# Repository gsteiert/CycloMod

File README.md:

# CycloMod
Cyclone 10LP plus RP2350 in SparkFun MicroMod form-factor

Be sure to subscribe to the [Cyclomod Crowd Supply Campaign](https://www.crowdsupply.com/steiert-solutions/cyclomod) for updates on when and how to get CycloMod.

CycloMod brings the flexibility of an FPGA to the SparkFun MicroMod ecosystem.  It combines the Raspberry Pi RP2350 with the Altera Cyclone 10LP, in a compact, adaptable module.  

The FPGA and MCU are designed to be used together.  Most of the MicroMod I/O are connected to the FPGA for highest flexibility, while some functions like USB, ADC and SWD take advantage of the dedicated peripherals in the RP2350.  A few signals, like reset and the primary I2C bus, are connected to both devices.

Most of the RP2350 I/O are connected to Cyclone 10LP.  The MCU is connected to the JTAG pins of the FPGA so that the same flash can store the MCU firmware and FPGA images to be loaded with the Altera JBC player.  GPIO on the FPGA are connected to the MCU QSPI interface to provide a reasonable speed data path between the two devices.  The HSTX port is also connected for higher speed streaming from the MCU to the FPGA.  Input and Output clocks are also connected between the two devices to allow for sharing the 12MHz refernce crystal from the MCU and PLLs in the FPGA.  

The primary intended use case is for the RP2350 to manage the loading of the FPGA to eliminate the need for an additional storage device.  The active serial configuration pins are connected to the SPI port pins on the MicroMod card edge and there is a solder bridge selector that can be cut and shorted to enable laoding the FPGA from external SPI flash.

FPGA images can be transfered to flash over USB using the UF2 flash loader built into the RP2350 ROM.  Altera provides a [JAM Byte Code player](https://github.com/steieio/altera-jbc-player) that can be used to load the FPGA over JTAG.  A [script is available to combine the JBC file with the RP2350 firmware in a single UF2 file](https://github.com/steieio/jbcuf2).  This methodology was demonstrated in the ["Build a $5 FPGA loader" workshop at Crowd Supply Teardown 2024](https://www.crowdsupply.com/teardown/portland-2024/workshop/build-a-5-fpga-loader).

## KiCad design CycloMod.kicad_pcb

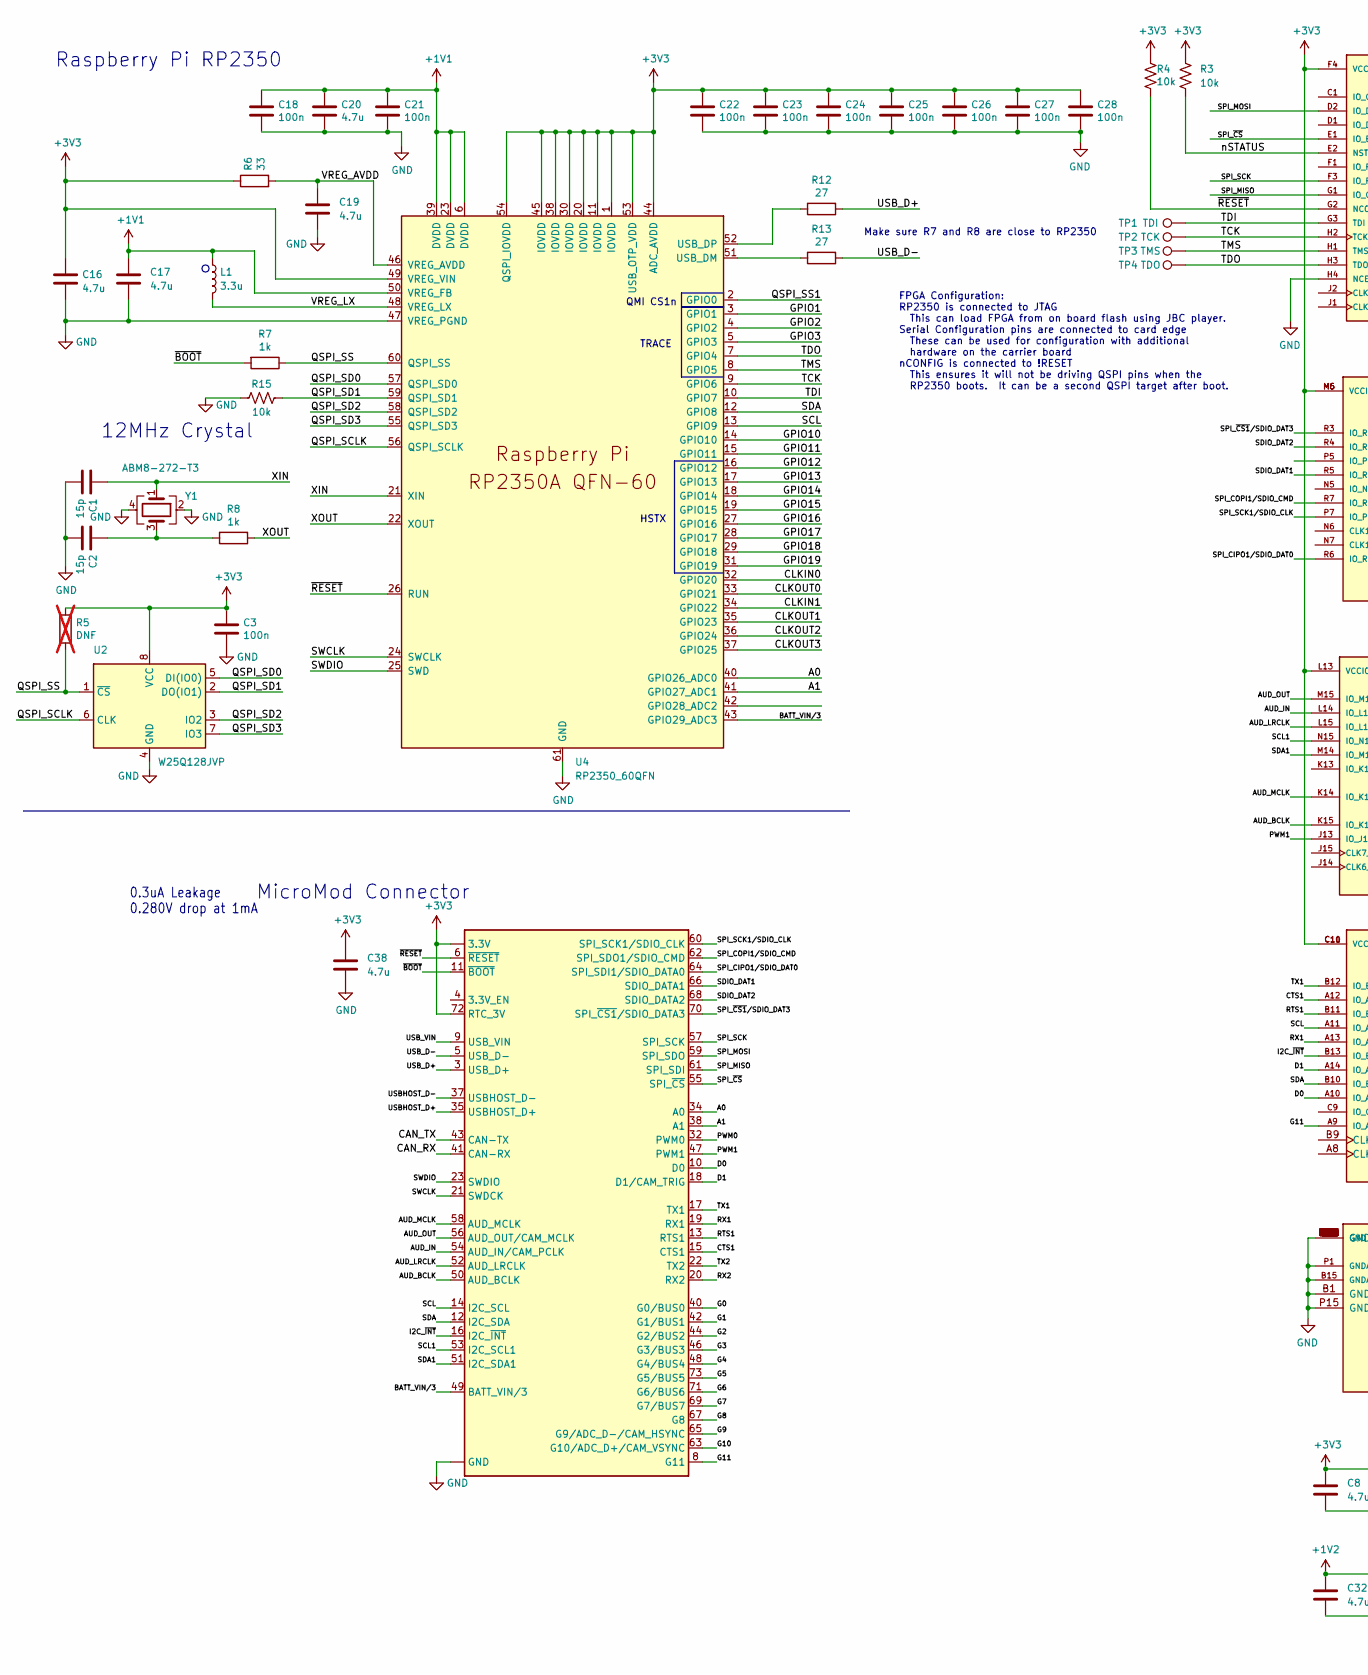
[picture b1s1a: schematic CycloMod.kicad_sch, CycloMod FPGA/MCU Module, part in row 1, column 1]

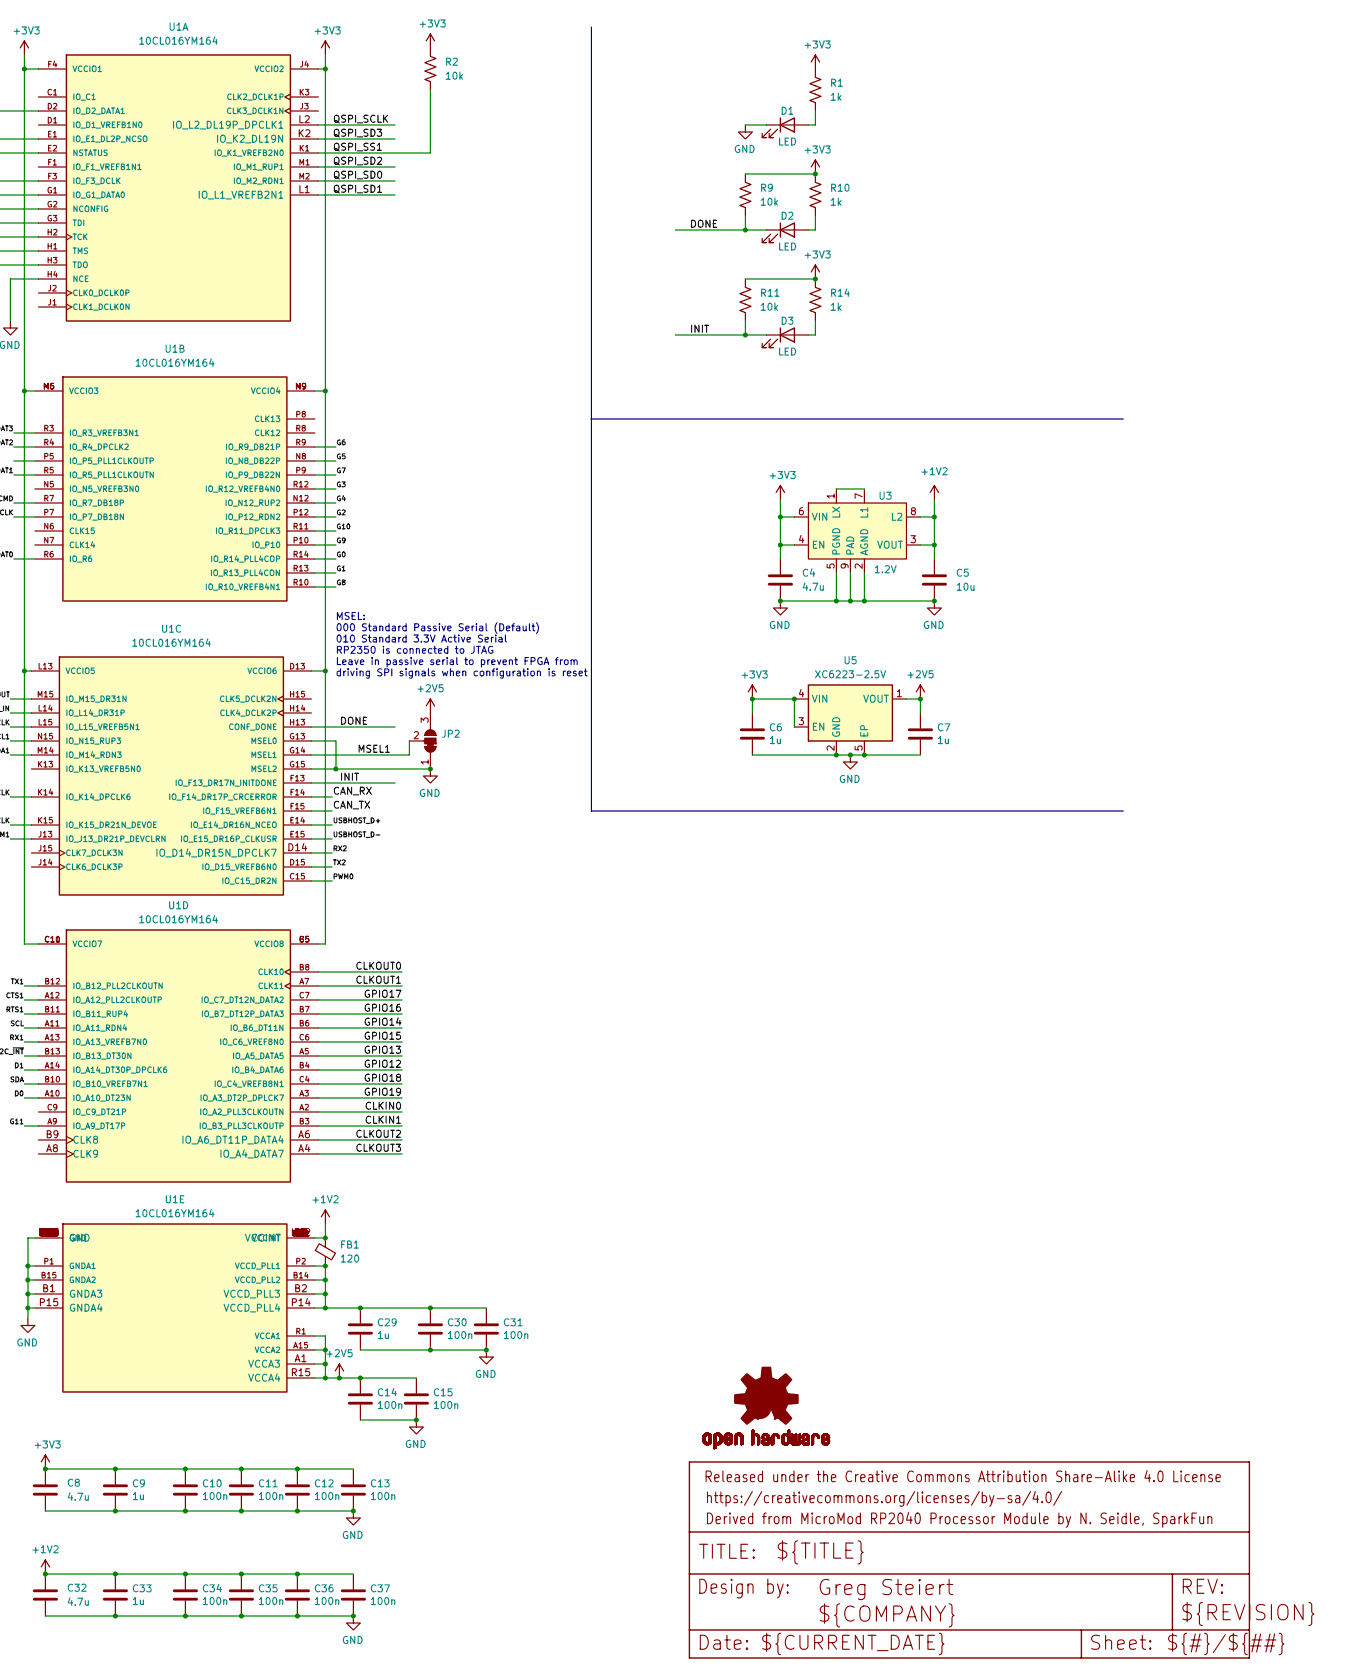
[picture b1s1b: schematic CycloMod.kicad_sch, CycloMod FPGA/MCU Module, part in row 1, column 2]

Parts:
C1, C2: 15p; C_0201_0603Metric; MPN CC0201JRNPO9BN150; LCSC C277480
C3, C10, C11, C12, C13, C14, C15, C18, C21, C22, C23, C24, C25, C26, C27, C28, C30, C31, C34, C35, C36, C37: 100n; C_0201_0603Metric; MPN GRM033R61A104KE15D; LCSC C76934
C4, C8, C19, C20, C32, C38: 4.7u; C_0402_1005Metric; MPN CL05A475MQ5NRNC; LCSC C307423
C5: 10u; C_0402_1005Metric; MPN CL05A106MQ5NUNC; LCSC C15525
C6, C7, C9, C29, C33: 1u; C_0402_1005Metric; MPN CL05A105KP5NNNC; LCSC C14445
C16, C17: 4.7u; C_0402_1005Metric_small_pads; MPN CL05A475MQ5NRNC; LCSC C307423
D1, D2, D3: LED; LED_0402_1005Metric; MPN IN-S42BT5B; LCSC C6968967
FB1: 120; R_0402_1005Metric; MPN BLM15AG121SN1D; LCSC C85812
FRAME1: FRAME-LEDGER; CREATIVE_COMMONS
J1: MICROMOD-2222; MicroMod_Processor
JP2: SolderJumper_3_Bridged12; SolderJumper-3pin_Bridged_RoundedPad_0402
L1: 3.3u; L_pol_2016; MPN AOTA-B201610S3R3-101-T; LCSC C42411119
LOGO3: OSHW-LOGOMINI; OSHW-LOGO-MINI
R1, R7, R8, R10, R14: 1k; R_0201_0603Metric; MPN RC0201FR-071KL; LCSC C138165
R2, R3, R4, R9, R11, R15: 10k; R_0201_0603Metric; MPN RC0201FR-0710KL; LCSC C106225
R5: DNF; R_0201_0603Metric; not fitted
R6: 33; R_0201_0603Metric; MPN RC0201FR-0733RL; LCSC C295794
R12, R13: 27; R_0201_0603Metric; MPN RC0201FR-0727RL; LCSC C273268
TP1: TDI; TestPoint_Pad_D0.5mm
TP2: TCK; TestPoint_Pad_D0.5mm
TP3: TMS; TestPoint_Pad_D0.5mm
TP4: TDO; TestPoint_Pad_D0.5mm
U1: 10CL016YM164; M164_8.0x8.0mm_0.5mm; PARTREV 2019.03.29; LCSC C6063581
U2: W25Q128JVP; WSON-8-1EP_6x5mm_P1.27mm_EP3.4x4.3mm; MPN W25Q128JVPIQ; LCSC C190862
U3: 1.2V; CL-2025-02; MPN XCL239B123FR-G; LCSC C6036085
U4: RP2350_60QFN; RP2350-QFN-60-1EP_7x7_P0.4mm_EP3.4x3.4mm_ThermalVias; MPN RP2350A; LCSC C42411118
U5: XC6223-2.5V; UDFN-4-1EP_1x1mm_P0.65mm_EP0.48x0.48mm; MPN XC6233H2519R-G; LCSC C6934286
Y1: ABM8-272-T3; Crystal_SMD_3225-4Pin_3.2x2.5mm; MPN ABM8-272-T3; LCSC C20625731

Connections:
+1V1: C17.1, C18.1, C20.1, C21.1, L1.1, U4.6 (DVDD), U4.23 (DVDD), U4.39 (DVDD), U4.50 (VREG_FB)
+1V2: C5.1, C32.1, C33.1, C34.1, C35.1, C36.1, C37.1, FB1.1, U1.D3 (VCCINT), U1.D6 (VCCINT), U1.D8 (VCCINT), U1.D10 (VCCINT), U1.F12 (VCCINT), U1.H12 (VCCINT), U1.K12 (VCCINT), U1.L3 (VCCINT), U1.M8 (VCCINT), U1.M11 (VCCINT), U1.N2 (VCCINT), U1.P3 (VCCINT), U3.3 (VOUT), U3.8 (L2)
+2V5: C7.1, C14.1, C15.1, JP2.3 (B), U1.A1 (VCCA3), U1.A15 (VCCA2), U1.R1 (VCCA1), U1.R15 (VCCA4), U5.1 (VOUT)
+3V3: C3.1, C4.1, C6.1, C8.1, C9.1, C10.1, C11.1, C12.1, C13.1, C16.1, C22.1, C23.1, C24.1, C25.1, C26.1, C27.1, C28.1, C38.1, J1.2 (3.3V), J1.72 (RTC_3V), J1.74 (3.3V), R1.1, R2.1, R3.1, R4.1, R5.1, R6.1, R9.1, R10.1, R11.1, R14.1, U1.B5 (VCCIO8), U1.C5 (VCCIO8), U1.C10 (VCCIO7), U1.C11 (VCCIO7), U1.D13 (VCCIO6), U1.F4 (VCCIO1), U1.J4 (VCCIO2), U1.L13 (VCCIO5), U1.M5 (VCCIO3), U1.M6 (VCCIO3), U1.M9 (VCCIO4), U1.N9 (VCCIO4), U2.8 (VCC), U3.4 (EN), U3.6 (VIN), U4.1 (IOVDD), U4.11 (IOVDD), U4.20 (IOVDD), U4.30 (IOVDD), U4.38 (IOVDD), U4.44 (ADC_AVDD), U4.45 (IOVDD), U4.49 (VREG_VIN), U4.53 (USB_OTP_VDD), U4.54 (QSPI_IOVDD), U5.3 (EN), U5.4 (VIN)
/A0: J1.34 (A0), U4.40 (GPIO26_ADC0)
/A1: J1.38 (A1), U4.41 (GPIO27_ADC1)
/AUD_BCLK: J1.50 (AUD_BCLK), U1.K15 (IO_K15_DR21N_DEVOE)
/AUD_IN: J1.54 (AUD_IN/CAM_PCLK), U1.L14 (IO_L14_DR31P)
/AUD_LRCLK: J1.52 (AUD_LRCLK), U1.L15 (IO_L15_VREFB5N1)
/AUD_MCLK: J1.58 (AUD_MCLK), U1.K14 (IO_K14_DPCLK6)
/AUD_OUT: J1.56 (AUD_OUT/CAM_MCLK), U1.M15 (IO_M15_DR31N)
/BATT_VIN/3: J1.49 (BATT_VIN/3), U4.43 (GPIO29_ADC3)
/CAN_RX: J1.41 (CAN-RX), U1.F14 (IO_F14_DR17P_CRCERROR)
/CAN_TX: J1.43 (CAN-TX), U1.F15 (IO_F15_VREFB6N1)
/CLKIN0: U1.A2 (IO_A2_PLL3CLKOUTN), U4.32 (GPIO20)
/CLKIN1: U1.B3 (IO_B3_PLL3CLKOUTP), U4.34 (GPIO22)
/CLKOUT0: U1.B8 (CLK10), U4.33 (GPIO21)
/CLKOUT1: U1.A7 (CLK11), U4.35 (GPIO23)
/CLKOUT2: U1.A6 (IO_A6_DT11P_DATA4), U4.36 (GPIO24)
/CLKOUT3: U1.A4 (IO_A4_DATA7), U4.37 (GPIO25)
/CTS1: J1.15 (CTS1), U1.A12 (IO_A12_PLL2CLKOUTP)
/D0: J1.10 (D0), U1.A10 (IO_A10_DT23N)
/D1: J1.18 (D1/CAM_TRIG), U1.A14 (IO_A14_DT30P_DPCLK6)
/DONE: D2.1 (K), R9.2, U1.H13 (CONF_DONE)
/G0: J1.40 (G0/BUS0), U1.R14 (IO_R14_PLL4COP)
/G1: J1.42 (G1/BUS1), U1.R13 (IO_R13_PLL4CON)
/G2: J1.44 (G2/BUS2), U1.P12 (IO_P12_RDN2)
/G3: J1.46 (G3/BUS3), U1.R12 (IO_R12_VREFB4N0)
/G4: J1.48 (G4/BUS4), U1.N12 (IO_N12_RUP2)
/G5: J1.73 (G5/BUS5), U1.N8 (IO_N8_DB22P)
/G6: J1.71 (G6/BUS6), U1.R9 (IO_R9_DB21P)
/G7: J1.69 (G7/BUS7), U1.P9 (IO_P9_DB22N)
/G8: J1.67 (G8), U1.R10 (IO_R10_VREFB4N1)
/G9: J1.65 (G9/ADC_D-/CAM_HSYNC), U1.P10 (IO_P10)
/G10: J1.63 (G10/ADC_D+/CAM_VSYNC), U1.R11 (IO_R11_DPCLK3)
/G11: J1.8 (G11), U1.A9 (IO_A9_DT17P)
/GPIO1: U4.3 (GPIO1)
/GPIO2: U4.4 (GPIO2)
/GPIO3: U4.5 (GPIO3)
/GPIO10: U4.14 (GPIO10)
/GPIO11: U4.15 (GPIO11)
/GPIO12: U1.B4 (IO_B4_DATA6), U4.16 (GPIO12)
/GPIO13: U1.A5 (IO_A5_DATA5), U4.17 (GPIO13)
/GPIO14: U1.B6 (IO_B6_DT11N), U4.18 (GPIO14)
/GPIO15: U1.C6 (IO_C6_VREF8N0), U4.19 (GPIO15)
/GPIO16: U1.B7 (IO_B7_DT12P_DATA3), U4.27 (GPIO16)
/GPIO17: U1.C7 (IO_C7_DT12N_DATA2), U4.28 (GPIO17)
/GPIO18: U1.C4 (IO_C4_VREFB8N1), U4.29 (GPIO18)
/GPIO19: U1.A3 (IO_A3_DT2P_DPLCK7), U4.31 (GPIO19)
/I2C_~INT: J1.16 (I2C_~INT), U1.B13 (IO_B13_DT30N)
/INIT: D3.1 (K), R11.2, U1.F13 (IO_F13_DR17N_INITDONE)
/MSEL1: JP2.2 (C), U1.G14 (MSEL1)
/PWM0: J1.32 (PWM0), U1.C15 (IO_C15_DR2N)
/PWM1: J1.47 (PWM1), U1.J13 (IO_J13_DR21P_DEVCLRN)
/QSPI_SCLK: U1.L2 (IO_L2_DL19P_DPCLK1), U2.6 (CLK), U4.56 (QSPI_SCLK)
/QSPI_SD0: U1.M2 (IO_M2_RDN1), U2.5 (DI(IO0)), U4.57 (QSPI_SD0)
/QSPI_SD1: R15.2, U1.L1 (IO_L1_VREFB2N1), U2.2 (DO(IO1)), U4.59 (QSPI_SD1)
/QSPI_SD2: U1.M1 (IO_M1_RUP1), U2.3 (IO2), U4.58 (QSPI_SD2)
/QSPI_SD3: U1.K2 (IO_K2_DL19N), U2.7 (IO3), U4.55 (QSPI_SD3)
/QSPI_SS: R5.2, R7.1, U2.1 (~CS), U4.60 (QSPI_SS)
/QSPI_SS1: R2.2, U1.K1 (IO_K1_VREFB2N0), U4.2 (GPIO0)
/RTS1: J1.13 (RTS1), U1.B11 (IO_B11_RUP4)
/RX1: J1.19 (RX1), U1.A13 (IO_A13_VREFB7N0)
/RX2: J1.20 (RX2), U1.D14 (IO_D14_DR15N_DPCLK7)
/SCL: J1.14 (I2C_SCL), U1.A11 (IO_A11_RDN4), U4.13 (GPIO9)
/SCL1: J1.53 (I2C_SCL1), U1.N15 (IO_N15_RUP3)
/SDA: J1.12 (I2C_SDA), U1.B10 (IO_B10_VREFB7N1), U4.12 (GPIO8)
/SDA1: J1.51 (I2C_SDA1), U1.M14 (IO_M14_RDN3)
/SDIO_DAT1: J1.66 (SDIO_DATA1), U1.R5 (IO_R5_PLL1CLKOUTN)
/SDIO_DAT2: J1.68 (SDIO_DATA2), U1.R4 (IO_R4_DPCLK2)
/SPI_CIPO1/SDIO_DAT0: J1.64 (SPI_SDI1/SDIO_DATA0), U1.R6 (IO_R6)
/SPI_COPI1/SDIO_CMD: J1.62 (SPI_SDO1/SDIO_CMD), U1.R7 (IO_R7_DB18P)
/SPI_MISO: J1.61 (SPI_SDI), U1.G1 (IO_G1_DATA0)
/SPI_MOSI: J1.59 (SPI_SDO), U1.D2 (IO_D2_DATA1)
/SPI_SCK: J1.57 (SPI_SCK), U1.F3 (IO_F3_DCLK)
/SPI_SCK1/SDIO_CLK: J1.60 (SPI_SCK1/SDIO_CLK), U1.P7 (IO_P7_DB18N)
/SPI_~CS1/SDIO_DAT3: J1.70 (SPI_~CS1/SDIO_DATA3), U1.R3 (IO_R3_VREFB3N1)
/SPI_~CS: J1.55 (SPI_~CS), U1.E1 (IO_E1_DL2P_NCSO)
/SWCLK: J1.21 (SWDCK), U4.24 (SWCLK)
/SWDIO: J1.23 (SWDIO), U4.25 (SWD)
/TCK: TP2.1, U1.H2 (TCK), U4.9 (GPIO6)
/TDI: TP1.1, U1.G3 (TDI), U4.10 (GPIO7)
/TDO: TP4.1, U1.H3 (TDO), U4.7 (GPIO4)
/TMS: TP3.1, U1.H1 (TMS), U4.8 (GPIO5)
/TX1: J1.17 (TX1), U1.B12 (IO_B12_PLL2CLKOUTN)
/TX2: J1.22 (TX2), U1.D15 (IO_D15_VREFB6N0)
/USBHOST_D+: J1.35 (USBHOST_D+), U1.E14 (IO_E14_DR16N_NCEO)
/USBHOST_D-: J1.37 (USBHOST_D-), U1.E15 (IO_E15_DR16P_CLKUSR)
/USB_D+: J1.3 (USB_D+), R12.1
/USB_D-: J1.5 (USB_D-), R13.1
/USB_VIN: J1.9 (USB_VIN)
/VREG_AVDD: C19.1, R6.2, U4.46 (VREG_AVDD)
/VREG_LX: L1.2, U4.48 (VREG_LX)
/XIN: C1.1, U4.21 (XIN), Y1.1
/XOUT: R8.1, U4.22 (XOUT)
/nSTATUS: R3.2, U1.E2 (NSTATUS)
/~BOOT: J1.11 (~BOOT), R7.2
/~RESET: J1.6 (~RESET), R4.2, U1.G2 (NCONFIG), U4.26 (RUN)
GND: C1.2, C2.2, C3.2, C4.2, C5.2, C6.2, C7.2, C8.2, C9.2, C10.2, C11.2, C12.2, C13.2, C14.2, C15.2, C16.2, C17.2, C18.2, C19.2, C20.2, C21.2, C22.2, C23.2, C24.2, C25.2, C26.2, C27.2, C28.2, C29.2, C30.2, C31.2, C32.2, C33.2, C34.2, C35.2, C36.2, C37.2, C38.2, D1.1 (K), J1.1 (GND), J1.7 (GND), J1.33 (GND), J1.36 (GND), J1.39 (GND), J1.45 (GND), J1.75 (GND), J1.GND, JP2.1 (A), R15.1, U1.B1 (GNDA3), U1.B15 (GNDA2), U1.C2 (GND), U1.C8 (GND), U1.C12 (GND), U1.C14 (GND), U1.D5 (GND), U1.D7 (GND), U1.D9 (GND), U1.D11 (GND), U1.E3 (GND), U1.E13 (GND), U1.F2 (GND), U1.G4 (GND), U1.G12 (GND), U1.G13 (MSEL0), U1.G15 (MSEL2), U1.H4 (NCE), U1.J12 (GND), U1.K4 (GND), U1.M3 (GND), U1.M7 (GND), U1.M10 (GND), U1.M13 (GND), U1.N1 (GND), U1.N4 (GND), U1.N10 (GND), U1.N11 (GND), U1.N14 (GND), U1.P1 (GNDA1), U1.P4 (GND), U1.P6 (GND), U1.P11 (GND), U1.P13 (GND), U1.P15 (GNDA4), U1.R2 (GND), U2.4 (GND), U3.2 (AGND), U3.5 (PGND), U3.9 (PAD), U4.47 (VREG_PGND), U4.61 (GND), U5.2 (GND), U5.5 (EP), Y1.2, Y1.4
unnamed: C2.1, R8.2, Y1.3
unnamed: D1.2 (A), R1.2
unnamed: D2.2 (A), R10.2
unnamed: D3.2 (A), R14.2
unnamed: C29.1, C30.1, C31.1, FB1.2, U1.B2 (VCCD_PLL3), U1.B14 (VCCD_PLL2), U1.P2 (VCCD_PLL1), U1.P14 (VCCD_PLL4)
unnamed: U3.1 (LX), U3.7 (L1)
unnamed: R13.2, U4.51 (USB_DM)
unnamed: R12.2, U4.52 (USB_DP)

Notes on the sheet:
MicroMod Connector
MSEL: 000 Standard Passive Serial (Default) 010 Standard 3.3V Active Serial RP2350 is connected to JTAG Leave in passive serial to prevent FPGA from driving SPI signals when configuration is reset
HSTX
0.3uA Leakage 0.280V drop at 1mA
Raspberry Pi RP2350
QMI CS1n
FPGA Configuration: RP2350 is connected to JTAG This can load FPGA from on board flash using JBC player. Serial Configuration pins are connected to card edge These can be used for configuration with additional hardware on the carrier board nCONFIG is connected to !RESET This ensures it will not be 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
Make sure R7 and R8 are close to RP2350
TRACE
12MHz Crystal

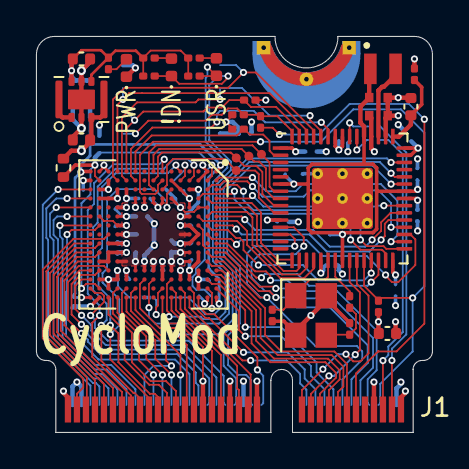
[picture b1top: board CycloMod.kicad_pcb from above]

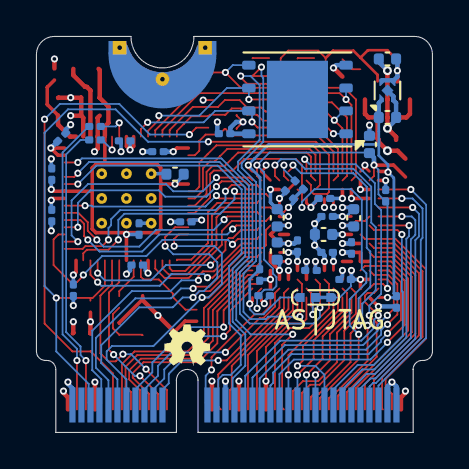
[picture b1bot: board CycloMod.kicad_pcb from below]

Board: 4 copper layers, 22.0 x 22.0 mm, 72 parts (37 on the bottom side), 101 nets.

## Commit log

2024-10-21 incremental edits
2024-10-26 signals connected, still need to place decoupling
2024-11-03 more routing and added decoupling caps for FPGA
2024-11-12 more cleanup, decoupling caps in, a couple nets need connecting, more cleanup to go
2024-11-28 checking in fully placed and routed. still needs silkscreen and cleanup
2024-12-23 started silkscreen cleanup, checking in prior to cardedge/outline update
2024-12-23 updated micromod footprint, more KiCad native
2024-12-24 remaped QSPI pins, checking in before moving flash
2024-12-24 all connected, cleaning up
2024-12-25 cleaning up nets
2024-12-25 cleaned up some DRC, modified mechanical mounting half hole
2025-07-30 commiting as submitted for build
2025-08-09 added project description and block-diagram to README
2025-08-09 updated block diagram
2026-01-01 fixed QMI SD1 pull-down, cleaned up notes
2026-01-01 fixed BOM and re-sync to pcb
2026-01-01 Turned off resistor silkscreen for R15
2026-01-25 moved block diagram to new img directory and added picture of board
2026-01-25 deleted file that was moved to img directory
2026-01-31 added link to campaign

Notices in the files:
CycloMod.kicad_pcb:
Released under the Creative Commons Attribution Share-Alike 4.0 License
https://creativecommons.org/licenses/by-sa/4.0
